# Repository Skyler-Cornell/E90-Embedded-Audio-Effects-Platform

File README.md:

# E90: Low Cost Embedded DSP Development Platform

The platform is designed for the development of DSP algorithms and provides the hardware and software infrastructure to get started writing programs manipulating real time audio signals in the C programming language. The board manages the analog audio input and output circuits, microcontroller peripherals, and the data flow, allowing a programmer to focus their efforts on designing DSP. The board was also designed wih musicians in mind, and can act as a programmable real time effects unit that players can plug their instruments into and run pre-compiled effects. An eventual goal of the project is to curate a growing library of pre-compiled firmware written by a community of developers that anyone can download and easily upload to the board to try out with their instruments. 

The board supports stereo 24bit audio at 48kHz sampling and implements a highly optimized DMA audio stream scheme. Refer to the Getting Started Manual pdf to ... get started using the platform.

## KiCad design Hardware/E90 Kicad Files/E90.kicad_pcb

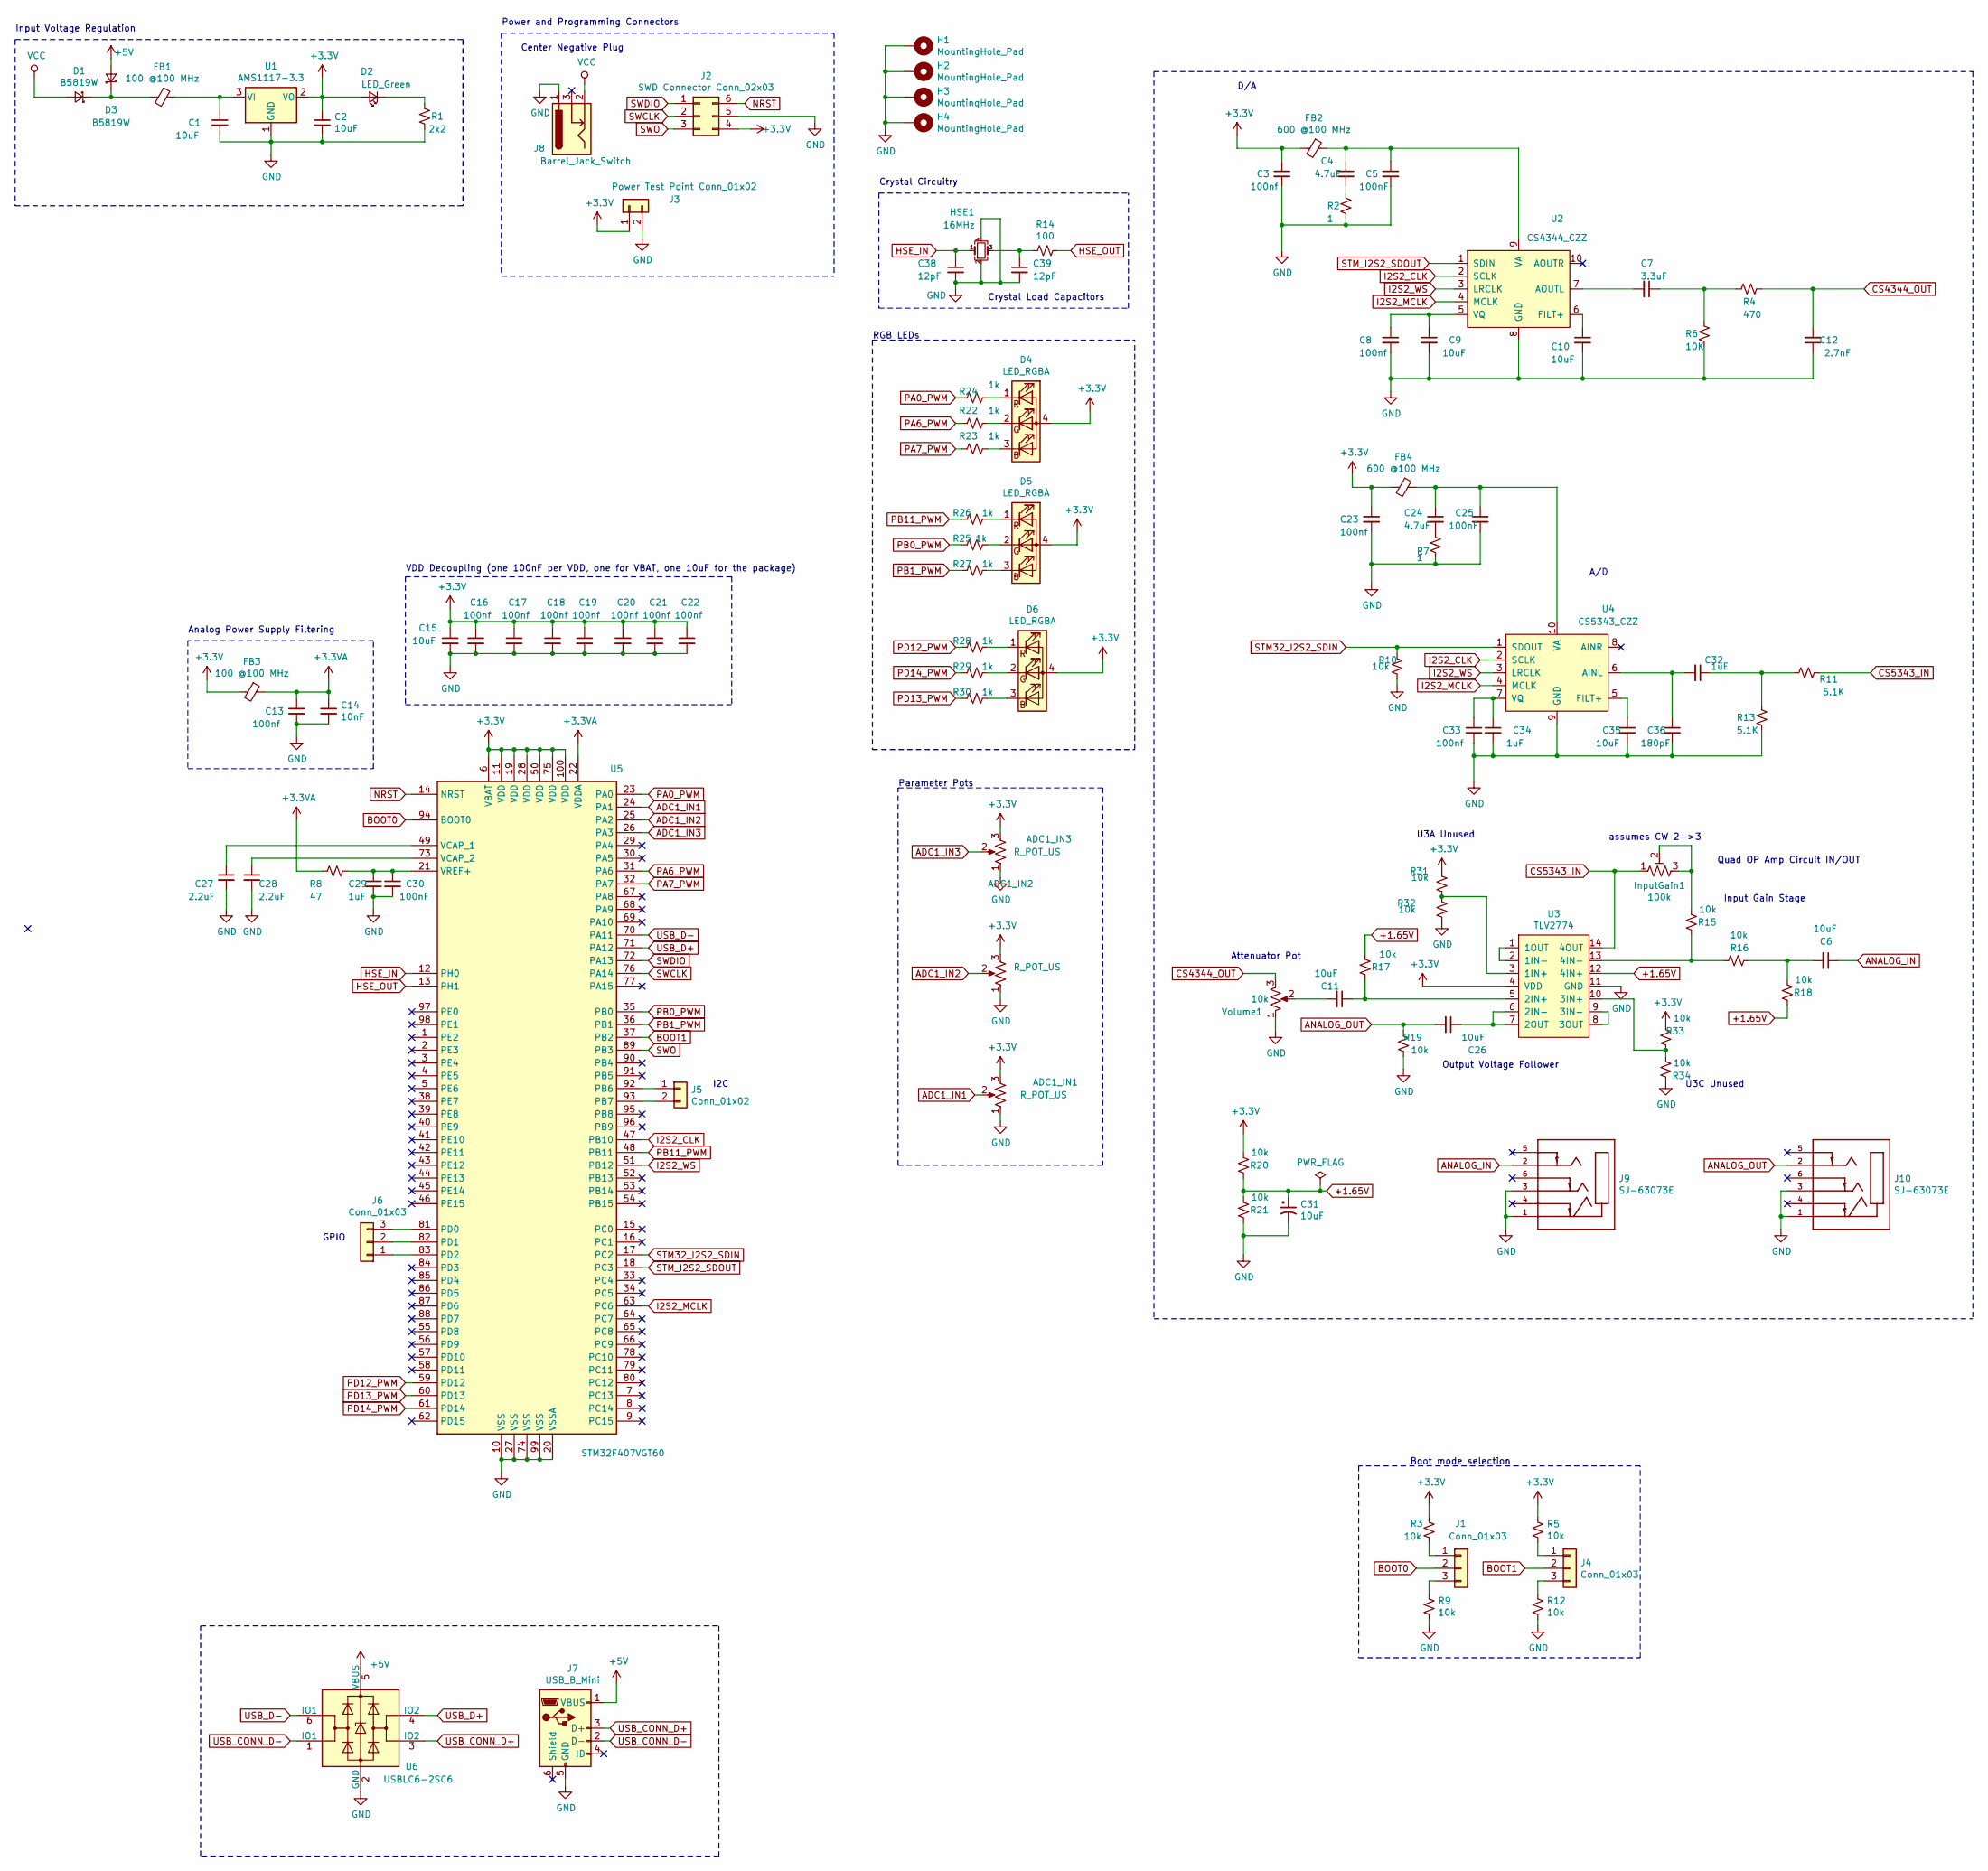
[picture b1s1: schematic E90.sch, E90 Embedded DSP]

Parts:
ADC1_IN1, ADC1_IN2, ADC1_IN3: R_POT_US; Potentiometer_Bourns_PTV09A-1_Single_Vertical
C1, C2: 10uF; C_0805_2012Metric; LCSC Part # C15850
C3, C8, C13, C16, C17, C18, C19, C20, C21, C22, C23, C33: 100nf; C_0402_1005Metric; LCSC Part # C1525
C4, C24: 4.7uF; C_0603_1608Metric; LCSC Part # C19666
C5, C25, C30: 100nF; C_0402_1005Metric; LCSC Part # C1525
C6, C9, C10, C11, C15, C26, C35: 10uF; C_0603_1608Metric; LCSC Part # C19702
C7: 3.3uF; C_0603_1608Metric; LCSC Part # C51412
C12: 2.7nF; C_0603_1608Metric; LCSC Part # C1609
C14: 10nF; C_0402_1005Metric; LCSC Part # C15195
C27, C28: 2.2uF; C_0603_1608Metric; LCSC Part # C23630
C29, C32, C34: 1uF; C_0603_1608Metric; LCSC Part # C15849
C31: 10uF; C_0805_2012Metric; LCSC C15850
C36: 180pF; C_0603_1608Metric; LCSC Part # C18437
C38, C39: 12pF; C_0402_1005Metric; LCSC Part # C1547
D1, D3: B5819W; D_SOD-123; LCSC Part # C8598
D2: LED_Green; LED_0603_1608Metric; LCSC Part # C72043
D4, D5, D6: LED_RGBA; 19-237-R6GHBHC-A01-2T; LCSC C60105
FB1, FB3: 100 @100 MHz; L_0805_2012Metric; LCSC Part # C1015
FB2, FB4: 600 @100 MHz; L_0805_2012Metric; LCSC Part # C1017
H1, H2, H3, H4: MountingHole_Pad; MountingHole_4.3mm_M4_Pad_Via
HSE1: 16MHz; Crystal_SMD_3225-4Pin_3.2x2.5mm; LCSC Part # C13738
InputGain1: 100k; Potentiometer_Piher_PT-10-V10_Vertical
J1, J4, J6: Conn_01x03; PinHeader_1x03_P2.54mm_Vertical
J2: SWD Connector Conn_02x03; PinHeader_2x03_P2.54mm_Vertical
J3: Power Test Point Conn_01x02; PinHeader_1x02_P2.54mm_Vertical
J5: Conn_01x02; PinHeader_1x02_P2.54mm_Vertical
J7: USB_B_Mini; USB_Mini-B_Lumberg_2486_01_Horizontal
J8: Barrel_Jack_Switch; BarrelJack_Horizontal
J9, J10: SJ-63073E; CUI_SJ-63073E; PARTREV 1.0
R1: 2k2; R_0603_1608Metric; LCSC Part # C4190
R2, R7: 1; R_0805_2012Metric; LCSC Part # C25271
R3, R5, R9, R10, R12: 10k; R_0603_1608Metric; LCSC Part # C25804
R4: 470; R_0603_1608Metric; LCSC Part # C23179
R6: 10K; R_0603_1608Metric; LCSC Part # C25804
R8: 47; R_0603_1608Metric; LCSC Part # C23182
R11, R13: 5.1K; R_0603_1608Metric; LCSC Part # C23186
R14: 100; R_0603_1608Metric; LCSC Part # C22775
R15, R16, R17, R18, R19, R20, R21, R31, R32, R33, R34: 10k; R_0603_1608Metric; LCSC Part # C23186
R22, R23, R24, R25, R26, R27, R28, R29, R30: 1k; R_0603_1608Metric; LCSC Part # C23182
U1: AMS1117-3.3; SOT-223-3_TabPin2; LCSC Part # C6186
U2: CS4344_CZZ; SOP50P490X110-10N
U3: TLV2774; DIP-14_W7.62mm_LongPads
U4: CS5343_CZZ; SOP50P490X110-10N
U5: STM32F407VGT60; LQFP-100_14x14mm_P0.5mm; LCSC Part # C12345
U6: USBLC6-2SC6; SOT-23-6; LCSC C7519
Volume1: 10k; Potentiometer_Bourns_PTV09A-1_Single_Vertical

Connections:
+1.65V: C31.1, R17.1, R18.2, R20.2, R21.1, U3.12 (4IN+)
+3.3VA: C13.1, C14.1, FB3.1, R8.1, U5.22 (VDDA)
+3V3: ADC1_IN1.3, ADC1_IN2.3, ADC1_IN3.3, C2.1, C3.1, C15.1, C16.1, C17.1, C18.1, C19.1, C20.1, C21.1, C22.1, C23.1, D2.2 (A), D4.4 (A), D5.4 (A), D6.4 (A), FB2.2, FB3.2, FB4.2, J2.4, J3.1, R3.2, R5.2, R20.1, R31.1, R33.1, U1.2 (VO), U3.4 (VDD), U5.6 (VBAT), U5.11 (VDD), U5.19 (VDD), U5.28 (VDD), U5.50 (VDD), U5.75 (VDD), U5.100 (VDD); also elsewhere on the board
+5V: D3.2 (A), J7.1 (VBUS), U6.5 (VBUS)
ADC1_IN1: ADC1_IN1.2, U5.24 (PA1)
ADC1_IN2: ADC1_IN2.2, U5.25 (PA2)
ADC1_IN3: ADC1_IN3.2, U5.26 (PA3)
ANALOG_IN: C6.1, J9.2
ANALOG_OUT: C26.2, J10.2, R19.1
BOOT0: J1.2, U5.94 (BOOT0)
BOOT1: J4.2, U5.37 (PB2)
CS4344_OUT: C12.2, R4.2, Volume1.3; also elsewhere on the board
CS5343_IN: InputGain1.1, R11.1, U3.14 (4OUT)
GND: ADC1_IN1.1, ADC1_IN2.1, ADC1_IN3.1, C1.2, C2.2, C3.2, C5.2, C8.2, C9.2, C10.2, C12.1, C13.2, C14.2, C15.2, C16.2, C17.2, C18.2, C19.2, C20.2, C21.2, C22.2, C23.2, C25.2, C27.2, C28.2, C29.2, C30.2, C31.2, C33.2, C34.2, C35.2, C36.2, C38.2, C39.2, H1.1, H2.1, H3.1, H4.1, HSE1.2, HSE1.4, J2.5, J3.2, J7.5 (GND), J8.1, J9.1, J9.3, J10.1, J10.3, R1.2, R2.1, R6.1, R7.1, R9.1, R10.1, R12.1, R13.1, R19.2, R21.2, R32.2, R34.2, U1.1 (GND), U2.8 (GND), U3.11 (GND), U4.9 (GND), U5.10 (VSS), U5.20 (VSSA), U5.27 (VSS), U5.74 (VSS), U5.99 (VSS), U6.2 (GND), Volume1.1; also elsewhere on the board
HSE_IN: C38.1, HSE1.1, U5.12 (PH0)
HSE_OUT: R14.2, U5.13 (PH1)
I2S2_CLK: U2.2 (SCLK), U4.2 (SCLK), U5.47 (PB10)
I2S2_MCLK: U2.4 (MCLK), U4.4 (MCLK), U5.63 (PC6)
I2S2_WS: U2.3 (LRCLK), U4.3 (LRCLK), U5.51 (PB12)
NRST: J2.6, U5.14 (NRST); also elsewhere on the board
unnamed: C1.1, FB1.1, U1.3 (VI)
unnamed: C4.1, C5.1, FB2.1, U2.9 (VA)
unnamed: C4.2, R2.2
unnamed: C6.2, R16.2, R18.1
unnamed: C7.1, R4.1, R6.2
unnamed: C7.2, U2.7 (AOUTL)
unnamed: C8.1, C9.1, U2.5 (VQ)
unnamed: C10.1, U2.6 (FILT+)
unnamed: C11.1, R17.2, U3.5 (2IN+)
unnamed 29: C11.2, Volume1.2; also elsewhere on the board
unnamed: C24.1, C25.1, FB4.1, U4.10 (VA)
unnamed: C24.2, R7.2
unnamed: C26.1, U3.6 (2IN-), U3.7 (2OUT)
unnamed: C27.1, U5.49 (VCAP_1)
unnamed: C28.1, U5.73 (VCAP_2)
unnamed: C29.1, C30.1, R8.2, U5.21 (VREF+)
unnamed: C32.1, R11.2, R13.2
unnamed: C32.2, C36.1, U4.6 (AINL)
unnamed: C33.1, C34.1, U4.7 (VQ)
unnamed: C35.1, U4.5 (FILT+)
unnamed: C39.1, HSE1.3, R14.1
unnamed: D1.1 (K), D3.1 (K), FB1.2
unnamed 42: D2.1 (K), R1.1; also elsewhere on the board
unnamed: D4.1 (RK), R24.2
unnamed: D4.2 (GK), R22.2
unnamed: D4.3 (BK), R23.2
unnamed: D5.1 (RK), R26.2
unnamed: D5.2 (GK), R25.2
unnamed: D5.3 (BK), R27.2
unnamed: D6.1 (RK), R28.2
unnamed: D6.2 (GK), R29.2
unnamed: D6.3 (BK), R30.2
unnamed: InputGain1.2, InputGain1.3, R15.1
unnamed: J1.1, R3.1
unnamed: J1.3, R9.2
unnamed: J4.1, R5.1
unnamed: J4.3, R12.2
unnamed: J5.1, U5.92 (PB6)
unnamed: J5.2, U5.93 (PB7)
unnamed: J6.1, U5.83 (PD2)
unnamed: J6.2, U5.82 (PD1)
unnamed: J6.3, U5.81 (PD0)
unnamed: R15.2, R16.1, U3.13 (4IN-)
unnamed: R31.2, R32.1, U3.3 (1IN+)
unnamed: R33.2, R34.1, U3.10 (3IN+)
unnamed: U3.1 (1OUT), U3.2 (1IN-)
unnamed: U3.8 (3OUT), U3.9 (3IN-)
PA0_PWM: R24.1, U5.23 (PA0)
PA6_PWM: R22.1, U5.31 (PA6)
PA7_PWM: R23.1, U5.32 (PA7)
PB0_PWM: R25.1, U5.35 (PB0)
PB1_PWM: R27.1, U5.36 (PB1)
PB11_PWM: R26.1, U5.48 (PB11)
PD12_PWM: R28.1, U5.59 (PD12)
PD13_PWM: R30.1, U5.60 (PD13)
PD14_PWM: R29.1, U5.61 (PD14)
STM32_I2S2_SDIN: R10.2, U4.1 (SDOUT), U5.17 (PC2)
STM_I2S2_SDOUT: U2.1 (SDIN), U5.18 (PC3)
SWCLK: J2.2, U5.76 (PA14); also elsewhere on the board
SWDIO: J2.1, U5.72 (PA13); also elsewhere on the board
SWO: J2.3, U5.89 (PB3); also elsewhere on the board
USB_CONN_D+: J7.3 (D+), U6.3 (IO2)
USB_CONN_D-: J7.2 (D-), U6.1 (IO1)
USB_D+: U5.71 (PA12), U6.4 (IO2)
USB_D-: U5.70 (PA11), U6.6 (IO1)
VCC: D1.2 (A), J8.2

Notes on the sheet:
Power and Programming Connectors
Crystal Circuitry
D/A
Analog Power Supply Filtering
Crystal Load Capacitors
VDD Decoupling (one 100nF per VDD, one for VBAT, one 10uF for the package)
assumes CW 2->3
Attenuator Pot
Boot mode selection
Output Voltage Follower
Input Gain Stage
Parameter Pots
Quad OP Amp Circuit IN/OUT
RGB LEDs
Input Voltage Regulation
A/D
GPIO
I2C
Center Negative Plug
U3C Unused
U3A Unused

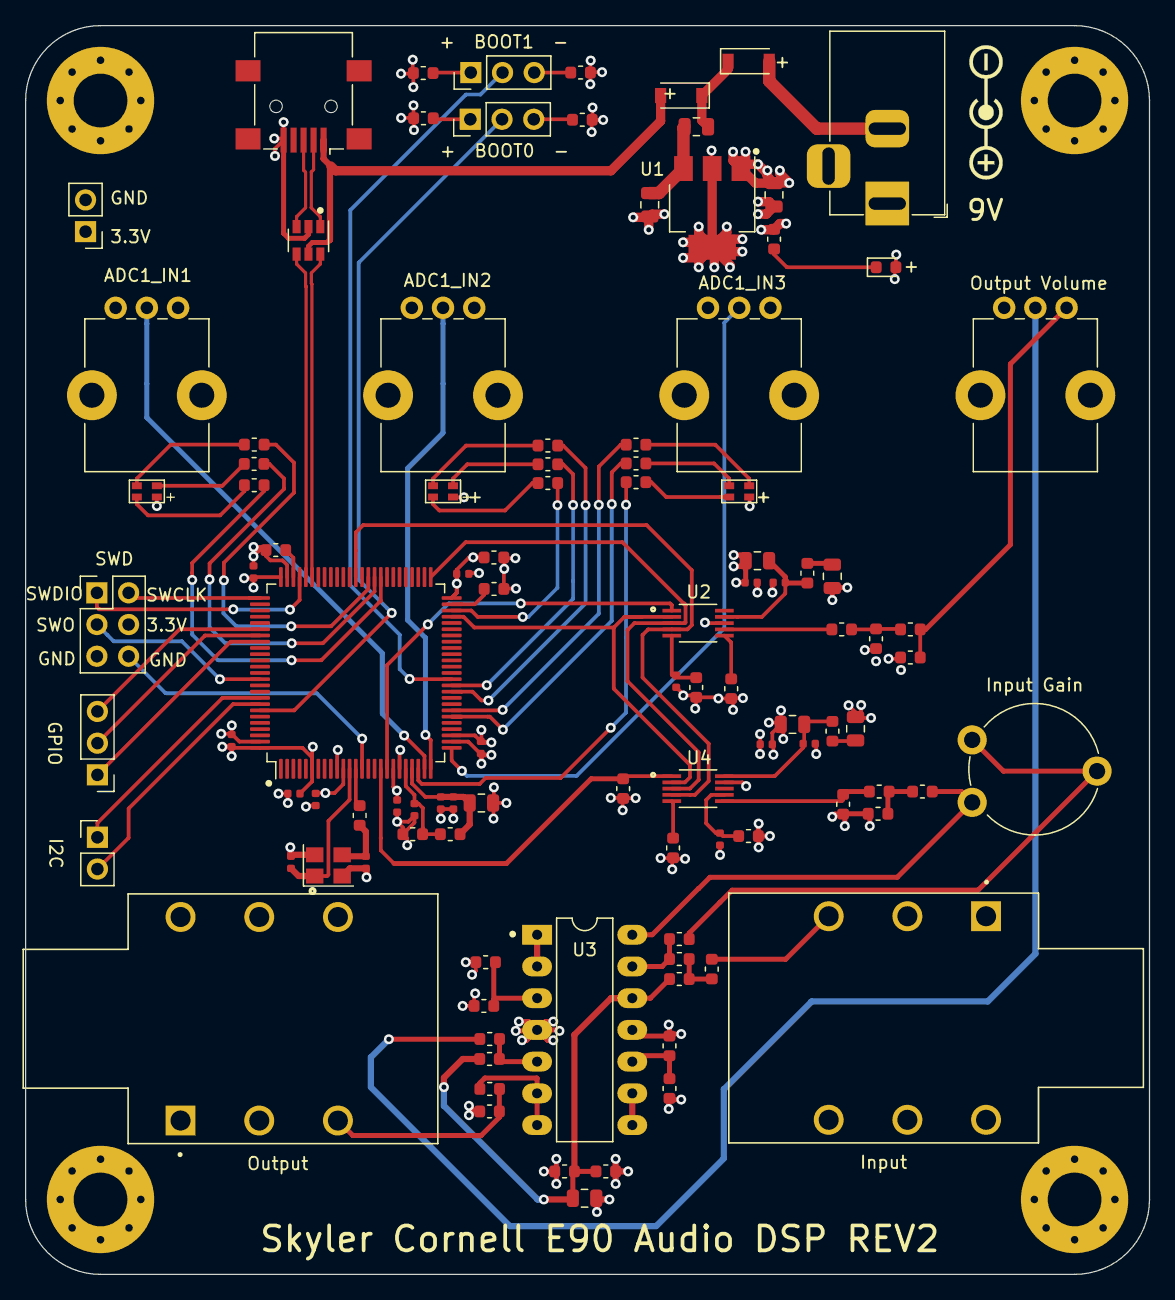
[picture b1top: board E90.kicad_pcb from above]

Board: 4 copper layers, 90.0 x 100.0 mm, 108 parts (0 on the bottom side), 86 nets.

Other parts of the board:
Output Volume: 10k; Potentiometer_Bourns_PTV09A-1_Single_Vertical
Power On: LED_Green; LED_0603_1608Metric
SWD: SWD Connector Conn_02x03; PinHeader_2x03_P2.54mm_Vertical

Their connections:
+3V3: Power On.2, SWD.4; also elsewhere on the board
CS4344_OUT: Output Volume.3; also elsewhere on the board
GND: Output Volume.1, SWD.5; also elsewhere on the board
NRST: SWD.6; also elsewhere on the board
unnamed 29: Output Volume.2; also elsewhere on the board
unnamed 42: Power On.1; also elsewhere on the board
SWCLK: SWD.2; also elsewhere on the board
SWDIO: SWD.1; also elsewhere on the board
SWO: SWD.3; also elsewhere on the board

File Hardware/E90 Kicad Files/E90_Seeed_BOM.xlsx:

Designator | Qty | Manufacturer Part Number or Seeed SKU | Link |  |  | Manufactorer |  | Footprint | Value
C1 C2 C31 | 3 | 302010158 | https://statics3.seeedstudio.com/fusion/opl/datasheet/302010158.pdf |  |  | YAGEO |  | 0805 | 10uF
C12 | 1 | 0603B272K500NT | https://file.elecfans.com/web1/M00/B0/EC/pIYBAF3vREiAa21yAA-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 |  |  | FH |  | 0603 | 2.7nF
C13 C17 C19 C21 C22 C16 C18 C20 C3 C8 C33 C23 | 12 | 302010024 | https://statics3.seeedstudio.com/fusion/opl/datasheet/302010024.pdf |  |  | YAGEO |  | 0402 | 100nf
C14 | 1 | 302010006 | https://statics3.seeedstudio.com/fusion/opl/datasheet/302010006.pdf |  |  | YAGEO |  | 0402 | 10nF
C15 C6 C11 C26 C9 C10 C35 | 7 | 302010103 | https://statics3.seeedstudio.com/fusion/opl/datasheet/302010103.pdf |  |  | YAGEO |  | 0603 | 10uF
C27 C28 | 2 | 302010054 | https://statics3.seeedstudio.com/fusion/opl/datasheet/302010054.pdf |  |  | YAGEO |  | 0603 | 2.2uF
C29 C34 C32 | 3 | 302010139 | https://statics3.seeedstudio.com/fusion/opl/datasheet/302010139.pdf |  |  | YAGEO |  | 0603 | 1uF
C30 C5 C25 | 3 | 302010024 | https://statics3.seeedstudio.com/fusion/opl/datasheet/302010024.pdf |  |  | YAGEO |  | 0402 | 100nF
C36 | 1 | 0603B181K500NT | https://file.elecfans.com/web1/M00/7D/4D/o4YBAFwKKSOANZPCAA-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 |  |  | FH |  | 0603 | 180pF
C38 C39 | 2 | 302010049 | https://statics3.seeedstudio.com/fusion/opl/datasheet/302010049.pdf |  |  | YAGEO |  | 0402 | 12pF
C4 C24 | 2 | 302010111 | https://statics3.seeedstudio.com/fusion/opl/datasheet/302010111.pdf |  |  | YAGEO |  | 0603 | 4.7uF
C7 | 1 | CL10A335KP8NNNC | https://file.elecfans.com/web1/M00/5C/4C/o4YBAFt04FWAbe4gAAK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 |  |  | SAMSUNG |  | 0603 | 3.3uF
R1 | 1 | 301010124 | https://statics3.seeedstudio.com/fusion/opl/datasheet/301010124.pdf |  |  | YAGEO |  | 0603 | 2k2
R11 R13 | 2 | 301010227 | https://statics3.seeedstudio.com/fusion/opl/datasheet/301010227.pdf |  |  | YAGEO |  | 0603 | 5.1K
R14 | 1 | 301010090 | https://statics3.seeedstudio.com/fusion/opl/datasheet/301010090.pdf |  |  | YAGEO |  | 0603 | 100
R16 R15 R18 R17 R19 R12 R5 R9 R3 R20 R21 R10 R33 R34 R31 R32 | 16 | 301010293 | https://statics3.seeedstudio.com/fusion/opl/datasheet/301010293.pdf |  |  | YAGEO |  | 0603 | 10k
R2 R7 | 2 | 0805W8F100KT5E | https://file.elecfans.com/web1/M00/61/0C/o4YBAFt-dwWACUP4AAh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 |  |  | Uniohm |  | 0805 | 1
R27 R26 R25 R24 R23 R22 R28 R29 R30 | 9 | 301010291 | https://statics3.seeedstudio.com/fusion/opl/datasheet/301010291.pdf |  |  | YAGEO |  | 0603 | 1k
R4 | 1 | 301010088 | https://statics3.seeedstudio.com/fusion/opl/datasheet/301010088.pdf |  |  | YAGEO |  | 0603 | 470
R6 | 1 | 301010293 | https://statics3.seeedstudio.com/fusion/opl/datasheet/301010293.pdf |  |  | YAGEO |  | 0603 | 10K
R8 | 1 | 301010091 | https://statics3.seeedstudio.com/fusion/opl/datasheet/301010091.pdf |  |  | YAGEO |  | 0603 | 47
U1 | 1 | AMS1117-3.3 | https://file.elecfans.com/web1/M00/B9/0E/pIYBAF57-siAbfa2AAF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 |  |  | AMS(美国) |  | SOT-223-3 | AMS1117-3.3
U2 | 1 | CS4344-CZZR | https://d3uzseaevmutz1.cloudfront.net/pubs/proDatasheet/CS43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 |  |  | Cirrus Logic |  | 10LD TSSOP | CS4344_CZZ
U5 | 1 | STM32F407VGT6 | https://www.mouser.com/datasheet/2/389/dm00037051-1797298.pdf |  |  | ST |  | LQPF-100 | STM32F407VGT60
U6 | 1 | USBLC6-2P6 | https://file.elecfans.com/web1/M00/7F/9E/pIYBAFwjN3uAIFePAAN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 |  |  | ST |  | SOT-23-6 | USBLC6-2SC6
D1 D3 | 2 | B5819W | https://file.elecfans.com/web1/M00/8A/32/pIYBAFyLiveAInCMAAt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 |  |  | MDD |  | SOD-123 | B5819W
D2 | 1 | LTST-C193KGKT-5A | https://file.elecfans.com/web1/M00/E7/12/pIYBAGBbCBiAIkcZAAs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 |  |  | Lite-On |  | 0603 | LED_Green
D5 D4 D6 | 3 | 19-237/R6GHBHC-A01/2T | https://file.elecfans.com/web1/M00/83/04/o4YBAFxJLzGANrbBAAN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 |  |  | Everlight |  | LED_SMD:19-237-R6GHBHC-A01-2T | LED_RGBA
FB2 FB4 | 2 | MPZ2012S101AT000 | https://file.elecfans.com/web1/M00/9E/A5/pIYBAF05UT6AJDrFAAL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 |  |  | TDK |  | 0805 | 100 @100 MHz
FB3 FB1 | 2 | MPZ2012S101AT000 | https://file.elecfans.com/web1/M00/9E/A5/pIYBAF05UT6AJDrFAAL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 |  |  | TDK |  | 0805 | 100 @100 MHz
HSE1 | 1 | X322516MLB4SI | https://file.elecfans.com/web1/M00/9A/01/o4YBAF0dzAaAAvQhABl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 |  |  | YXC |  | Crystal:Crystal_SMD_3225-4Pin_3.2x2.5mm | 16MHz

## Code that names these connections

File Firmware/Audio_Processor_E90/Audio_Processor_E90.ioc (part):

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Mcu.Name=STM32F407V(E-G)Tx
Mcu.Package=LQFP100
Mcu.UserName=STM32F407VGTx
PA0-WKUP.Signal=S_TIM2_CH1_ETR
PA1.Signal=ADCx_IN1
PA11.Mode=Device_Only
PA11.Signal=USB_OTG_FS_DM
PA12.Mode=Device_Only
PA12.Signal=USB_OTG_FS_DP
PA13.Mode=Trace_Asynchronous_SW
PA13.Signal=SYS_JTMS-SWDIO
PA14.Mode=Trace_Asynchronous_SW
PA14.Signal=SYS_JTCK-SWCLK
PA2.Signal=ADCx_IN2
PA3.Signal=ADCx_IN3
PA6.Signal=S_TIM3_CH1
PA7.Signal=S_TIM3_CH2
PB0.Signal=S_TIM3_CH3
PB1.Signal=S_TIM3_CH4
PB10.Mode=Full_Duplex_Master
PB10.Signal=I2S2_CK
PB11.Signal=S_TIM2_CH4
PB12.Mode=Full_Duplex_Master
PB12.Signal=I2S2_WS
PB3.Mode=Trace_Asynchronous_SW
PB3.Signal=SYS_JTDO-SWO
PB6.Mode=I2C
PB6.Signal=I2C1_SCL
PB7.Mode=I2C
PB7.Signal=I2C1_SDA
PC2.Mode=Full_Duplex_Master
PC2.Signal=I2S2_ext_SD
PC3.Mode=Full_Duplex_Master
PC3.Signal=I2S2_SD
PC6.Mode=Master_Clock_Activated
PC6.Signal=I2S2_MCK
PD0.Signal=GPIO_Output
PD1.Signal=GPIO_Output
PD12.Signal=S_TIM4_CH1
PD13.Signal=S_TIM4_CH2
PD14.Signal=S_TIM4_CH3
PD2.Signal=GPIO_Output
PE10.Signal=GPIO_Output
PE11.Signal=GPIO_Output
PE8.Signal=GPIO_Input
PE9.Signal=GPIO_Input
PH0-OSC_IN.Mode=HSE-External-Oscillator
PH0-OSC_IN.Signal=RCC_OSC_IN
PH1-OSC_OUT.Mode=HSE-External-Oscillator
PH1-OSC_OUT.Signal=RCC_OSC_OUT
RCC.HSE_VALUE=16000000
RCC.SYSCLKFreq_VALUE=168000000
RCC.SYSCLKSource=RCC_SYSCLKSOURCE_PLLCLK
board=custom

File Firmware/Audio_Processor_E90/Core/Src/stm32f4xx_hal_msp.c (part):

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  
    __HAL_RCC_GPIOA_CLK_ENABLE();
    /**ADC1 GPIO Configuration    
    PA1     ------> ADC1_IN1
    PA2     ------> ADC1_IN2
    PA3     ------> ADC1_IN3 
    */
    GPIO_InitStruct.Pin = GPIO_PIN_1|GPIO_PIN_2|GPIO_PIN_3;
    GPIO_InitStruct.Mode = GPIO_MODE_ANALOG;
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    __HAL_RCC_ADC1_CLK_DISABLE();
  
    /**ADC1 GPIO Configuration    
    PA1     ------> ADC1_IN1
    PA2     ------> ADC1_IN2
    PA3     ------> ADC1_IN3 
    */
    HAL_GPIO_DeInit(GPIOA, GPIO_PIN_1|GPIO_PIN_2|GPIO_PIN_3);

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  
    __HAL_RCC_GPIOB_CLK_ENABLE();
    /**I2C1 GPIO Configuration    
    PB6     ------> I2C1_SCL
    PB7     ------> I2C1_SDA 
    */
    GPIO_InitStruct.Pin = GPIO_PIN_6|GPIO_PIN_7;
    GPIO_InitStruct.Mode = GPIO_MODE_AF_OD;
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    __HAL_RCC_I2C1_CLK_DISABLE();
  
    /**I2C1 GPIO Configuration    
    PB6     ------> I2C1_SCL
    PB7     ------> I2C1_SDA 
    */
    HAL_GPIO_DeInit(GPIOB, GPIO_PIN_6|GPIO_PIN_7);

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    __HAL_RCC_GPIOC_CLK_ENABLE();
    __HAL_RCC_GPIOB_CLK_ENABLE();
    /**I2S2 GPIO Configuration    
    PC2     ------> I2S2_ext_SD
    PC3     ------> I2S2_SD
    PB10     ------> I2S2_CK
    PB12     ------> I2S2_WS
    PC6     ------> I2S2_MCK 
    */
    GPIO_InitStruct.Pin = GPIO_PIN_2;
    GPIO_InitStruct.Mode = GPIO_MODE_AF_PP;
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    __HAL_RCC_SPI2_CLK_DISABLE();
  
    /**I2S2 GPIO Configuration    
    PC2     ------> I2S2_ext_SD
    PC3     ------> I2S2_SD
    PB10     ------> I2S2_CK
    PB12     ------> I2S2_WS
    PC6     ------> I2S2_MCK 
    */
    HAL_GPIO_DeInit(GPIOC, GPIO_PIN_2|GPIO_PIN_3|GPIO_PIN_6);

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    __HAL_RCC_GPIOA_CLK_ENABLE();
    __HAL_RCC_GPIOB_CLK_ENABLE();
    /**TIM2 GPIO Configuration    
    PA0-WKUP     ------> TIM2_CH1
    PB11     ------> TIM2_CH4 
    */
    GPIO_InitStruct.Pin = GPIO_PIN_0;
    GPIO_InitStruct.Mode = GPIO_MODE_AF_PP;
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    __HAL_RCC_GPIOA_CLK_ENABLE();
    __HAL_RCC_GPIOB_CLK_ENABLE();
    /**TIM3 GPIO Configuration    
    PA6     ------> TIM3_CH1
    PA7     ------> TIM3_CH2
    PB0     ------> TIM3_CH3
    PB1     ------> TIM3_CH4 
    */
    GPIO_InitStruct.Pin = GPIO_PIN_6|GPIO_PIN_7;
    GPIO_InitStruct.Mode = GPIO_MODE_AF_PP;
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  
    __HAL_RCC_GPIOD_CLK_ENABLE();
    /**TIM4 GPIO Configuration    
    PD12     ------> TIM4_CH1
    PD13     ------> TIM4_CH2
    PD14     ------> TIM4_CH3 
    */
    GPIO_InitStruct.Pin = GPIO_PIN_12|GPIO_PIN_13|GPIO_PIN_14;
    GPIO_InitStruct.Mode = GPIO_MODE_AF_PP;
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  
    __HAL_RCC_GPIOA_CLK_ENABLE();
    /**USB_OTG_FS GPIO Configuration    
    PA11     ------> USB_OTG_FS_DM
    PA12     ------> USB_OTG_FS_DP 
    */
    GPIO_InitStruct.Pin = GPIO_PIN_11|GPIO_PIN_12;
    GPIO_InitStruct.Mode = GPIO_MODE_AF_PP;
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    __HAL_RCC_USB_OTG_FS_CLK_DISABLE();
  
    /**USB_OTG_FS GPIO Configuration    
    PA11     ------> USB_OTG_FS_DM
    PA12     ------> USB_OTG_FS_DP 
    */
    HAL_GPIO_DeInit(GPIOA, GPIO_PIN_11|GPIO_PIN_12);

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
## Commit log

2020-12-30 imported custom symbol libs from old directory all E90 project files can live in this directory
2020-12-30 added gitignore
2020-12-30 edited gitignore
2020-12-30 update untracked
2020-12-30 refactoring PCB
2020-12-31 finished pcb 1.0
2020-12-31 added ground pours on all 4 layers
2021-01-01 added pdf
2021-01-01 added audio IC data sheets to references
2021-01-02 Gerbers finalized for Rev1 znd sent to JLCPCB for fabrication
2021-01-02 included REV1 JLCPCB order invoice
2021-01-02 added directory for E90 expenses
2021-01-18 Ping Pong Buf working on custom board. have not tested passthrough yet
2021-01-21 added firmwre
2021-01-22 revisions to audio framework
2021-01-22 audio fraW working
2021-01-26 integrated faust generated delay effect and runs on custom board
2021-01-28 Faust oscillators working, needed to call process_init() before HAL_I2SEx_TransmitReceive_DMA(), otherwise dma interrupts start firing and audio processing before everything is initialized to 0
2021-03-28 started Pcb rev2
2021-04-05 Finished rev2 schem, now onto the PCB
2021-04-05 updated schem pdf
2021-04-07 PCB priog
2021-04-08 routing
2021-04-08 finished pcb
2021-04-12 added PCB image
2021-04-12 added PCB image to readme
2021-04-12 PCB image rename
2021-05-04 added image of REV2
2021-05-10 potentiometer IIR
2021-05-10 unstash
2021-05-20 Pushing Starter Template Project Code
2021-05-22 finished LED API for now
2021-05-26 LED and POT API working
2021-05-26 dfdfdfdf
2022-04-24 fixed pot orientation
2022-04-24 added WM8731 codec part to schem
2022-04-24 schem

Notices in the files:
Firmware/Audio_Processor_E90/Core/Src/stm32f4xx_hal_msp.c:
© Copyright (c) 2021 STMicroelectronics.
All rights reserved.
This software component is licensed by ST under BSD 3-Clause license,
the "License"; You may not use this file except in compliance with the
License. You may obtain a copy of the License at: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
(C) COPYRIGHT STMicroelectronics *****END OF FILE
